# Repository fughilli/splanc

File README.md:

<p align="center">

</p>

**Map every LED in an addressable-LED installation in 3D — with just a phone —
then design light effects that flow across the real geometry and play them live
on the controller.**

Mount your LEDs however you like (a sculpture, a ceiling, a sign, a tree), walk
around the lit fixture with your phone, and splanc recovers the `(x, y, z)`
position of every LED. Then you author effects in a browser editor and stream
them to the device, where they run across the fixture's true 3D shape instead of
a guessed layout.

No ARCore, no LiDAR, no depth sensor — capture runs in any modern phone browser
(rear camera + motion sensors), and a visual-inertial solver estimates the
camera path and the LED positions together.

<p align="center">
  
  <br />
  <em>▶ Watch the intro video</em>
</p>

## Quickstart

**→ [The Splanc quickstart](./docs/quickstart.md)**: from a bare ESP32-C6
board to mapped, animated lights in a browser. The app is a PWA, nothing to
install: **<https://splanc.io/app>**.

1. **Wire it.** Any ESP32-C6 board (the C6 SuperMini is the reference), a
   WS2812/NeoPixel strip with its data on **GPIO20** (a second strip on
   GPIO14), and a 5 V supply for the strip with a common ground.
2. **Flash it.** Open the app in Chrome or Edge on a computer (or Chrome on
   Android; the iPhone app can't set up new hardware), tap **Flash new device
   (USB)**, then **Connect a board & flash**. No toolchain needed.
3. **Put it on Wi-Fi.** **Add device (Bluetooth)**: enter your Wi-Fi, pick the
   board, and accept its certificate once. From firmware 1.10.0 it remembers
   the network across reboots and updates.
4. **Map it.** **Maps ▸ + New**, then walk slowly around the lit fixture with
   your phone until the live preview converges. You get a 3D map of every LED.
5. **Play.** Pick or write an effect, perform in Show mode, bind MIDI knobs, or
   hand the lights to your AI agent (below).

## Ask an AI agent

Splanc players can also be driven by an AI agent. Tell an agent that has a shell
and Node.js 20 or later _"Use splanc.io to set the mood of the room"_. It reads
<https://splanc.io/AGENTS.md> and finds every Splanc fixture on your LAN. It
treats them as one room, with a shared room frame and clock, and can tweak the
running effect's knobs or write, preview and deploy a new effect.

To install it as an MCP server once:

```sh
claude mcp add splanc -- npx -y https://splanc.io/agent/splanc-agent.tgz
```

There is no LAN authentication, so anyone on your network can drive the lights.
See [`agent/README.md`](./agent/README.md).

## Hardware

- **Controller:** an **ESP32-C6** running the firmware in [`firmware/`](./firmware),
  or a **Raspberry Pi** (see [`pi/`](./pi)). The controller drives the LEDs, runs
  the effects VM, and serves the secure control channel.
- **LEDs:** addressable strips or pixels (SK9822 / APA102 / WS2812-family).
- **Capture device:** any phone with a rear camera and motion sensors
  (Android / Chrome is the primary target).

## How it works

1. **Blink code.** The controller drives the LEDs through a short, self-clocking
   color code that gives every LED a unique temporal signature.
2. **Capture.** You walk around the fixture with the phone. The camera decodes
   each LED's code frame-by-frame while the phone's motion sensors track its
   pose.
3. **Solve.** A visual-inertial bundle adjustment recovers each LED's 3D
   position (and the camera trajectory), metric-scaled and gravity-aligned.
4. **Topology.** The point cloud is turned into a skeleton — strands, segments,
   junctions and loops — so effects can address the fixture by its shape, not
   just its coordinates.
5. **Effects.** You write GLSL-ish shaders in the browser editor (per-LED
   position, segment, distance fields, textures), preview them live, and the
   compiler emits compact bytecode.
6. **Play.** The bytecode runs on the controller's effects VM, streamed over a
   secure WebSocket — so what you see in the editor is what lights up.

## Learn more

- **Quickstart:** [`docs/quickstart.md`](./docs/quickstart.md) — wiring,
  flashing, Wi-Fi, mapping, effects and agents, one short section each
- **Using the app:** [`docs/user-guide.md`](./docs/user-guide.md) — a walkthrough of
  every feature (also an interactive tutorial in the app, from Settings ▸ Help)
- **Why it's built this way:** [the Splanc manifesto](./docs/manifesto.md):
  a microcontroller instead of Art-Net boxes, our own wireless stack, no heap,
  and model checking for an LED controller.
- **What's new:** [`docs/whats-new.md`](./docs/whats-new.md)
- **Contributing & building from source:** [`DEVELOPERS.md`](./DEVELOPERS.md)
- **Design & architecture:** [`led-mapper-design.md`](./led-mapper-design.md) —
  the durable spec — plus [`docs/`](./docs)
- **Project history / build log:** [`WORKLOG.md`](./WORKLOG.md)

## License

Splanc is free and open-source software, licensed under the
**[GNU Affero General Public License v3.0](./LICENSE)** (AGPL-3.0). Two subtrees
are carved out under the permissive **MIT License** so anyone can build
compatible projects against the wire protocol:

- **`shared/protocol/`** — the LED Mapper wire protocol (schemas, `.proto`, and
  the generated TypeScript/Python/Rust bindings).
- **`tools/touchdesigner/`** — the TouchDesigner client binding.

See [`LICENSING.md`](./LICENSING.md) for the full map. Contributions are welcome
under a [Contributor License Agreement](./CLA.md); start with
[`CONTRIBUTING.md`](./CONTRIBUTING.md).

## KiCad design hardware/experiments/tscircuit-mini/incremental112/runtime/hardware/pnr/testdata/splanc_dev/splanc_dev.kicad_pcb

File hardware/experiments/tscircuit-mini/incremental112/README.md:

# Incremental placement candidate evaluation

Clones the incumbent routed PCB, not the original unrouted source. The requested
run is seeded from full109's completed round01 (85 native opens, zero violations;
153 subwidth tracks and one unqualified pair remain). No baseline reroute.

incremental_place.py peels copper leaves touching moved pads back to the first
shared junction/stationary pad, preserves shared trunks, then invalidates exact
layer-aware pad/drill clearance conflicts at the destination. It retains all
unaffected track/via UUIDs and normalized geometry, plane definitions, outline,
and native footprint/pad identities. Bodies do not blanket-delete inner copper.
Locked copper and source-sized power arrays fail closed. Affected pairs are
invalidated together and their stale reference witnesses removed. The prototype
rejects outline changes and source-array/keepout owner relocation.

Full electrical phases continue against retained copper. Existing arrays are
retained; planes refill. Staged signals use fixed copper. Final candidate guards
compare original pad connectivity and qualified entries with the repaired board;
open-count improvement cannot conceal loss of a previously connected group.
The winner becomes the routed seed for the next round only on acceptance.
Each phase is captured, including the routed seed and local invalidation with
removed UUID/reason metadata. Batch111 deferred native DRC validation is included.

Tests: three native geometry regressions (shared T trunk/layer separation,
destination conflict, no-op exact copper). Real first-round C1 translation keeps
2043/2048 copper items. Real no-op keeps all2048 and native85opens/0violations.
Controller preflight resumes round2 with one completed round. Full experimental
routing and final visual/electrical qualification remain in progress.

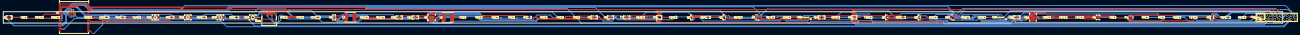
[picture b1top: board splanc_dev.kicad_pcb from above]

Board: 2 copper layers, 787.0 x 7.0 mm, 79 parts (0 on the bottom side), 54 nets.

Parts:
C1, C2, C3, C4, C8, C9, C12, C13, C14, C16, C17, C19, C20, C22, C23, C24, C25, C26: C0402
C5, C6, C7, C10, C11, C18, C21: C0805
C15, C27: C0603
CN1: CONN-TH_B2B-PH-K-S
CN2, CN3: CONN-TH_B3B-PH-K-S
H1: HDR-TH_20P-P2.54-V-M-R2-C10-S2.54
L1: L0805
L2, L3: IND-SMD_L6.0-W6.0_SWPA6045S
Q1, Q3: SOT-23-3_L2.9-W1.3-P1.90-LS2.4-BR
Q2, Q4: SOT-23_L2.9-W1.3-P1.90-LS2.4-BR
R1, R2, R3, R6, R7, R8, R9, R11, R12, R14, R16, R17, R18, R20, R21, R22, R23: R0402
R4, R5, R10, R13, R15, R19, R24, R25: R0603
SW1, SW2, SW3, SW4: SW-SMD_L3.9-W3.0-P4.45
U1: LGA-8_L2.5-W2.0-P0.65_AMP6127
U2: VQFN-20_L4.6-W3.6-P0.50-BL
U3: SOT-23-5_L3.0-W1.7-P0.95-LS2.8-BR
U4: SOT-23-5_L3.0-W1.7-P0.95-LS2.8-BL
U5: WIRELM-SMD_ESP32-C6-WROOM-1
U6: TDFN-8_L2.0-W2.0-P0.50-BL-EP1.2
U7, U9: MSOP-10_L3.0-W3.0-P0.50-LS5.0-BL
U8, U10: SOT-23-6_L2.9-W1.6-P0.95-LS2.8-BR
U11: QFN-24_L4.0-W4.0-P0.50-BL-EP2.7
USB1: USB-C-SMD_TYPE-C-16PIN-2MD-073

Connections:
1: H1.16, R5.2, SW1.1, U5.15
1-1: H1.17, R24.2, SW3.1, U5.20
1-2: H1.18, R25.2, SW4.1, U5.21
13: U5.13, USB1.A7, USB1.B7
14: U5.14, USB1.A6, USB1.B6
19: H1.19, U5.25
20: H1.20, U5.24
A5: R6.1, USB1.A5
B: Q1.1, R14.2
B5: R7.1, USB1.B5
BOOT: C3.2, U2.8
C: Q1.3, Q2.1, R15.2
COMP: C4.1, U2.18
CPOUT: C24.1, U11.20
EN: U2.2, U5.11
EN-1: C14.1, H1.15, R10.2, SW2.1, U5.3
FB: R1.1, R2.2, U2.17
FB-1: R11.1, R12.2, U3.5
FSW: R3.1, U2.3
ILIM: R4.1, U2.19
INT: U5.19, U11.12
PROG: R8.1, U4.5
REGOUT: C26.1, U11.10
RESV: U11.19, U11.21, U11.22
S: Q2.2, R15.1, R16.2, U7.8, U7.9
SCL: H1.14, R22.2, U1.4, U5.7, U6.7, U7.5, U9.5, U11.23
SDA: H1.13, R23.2, U1.3, U5.6, U6.8, U7.4, U9.4, U11.24
SS: C8.1, U2.10
STAT: R9.2, U4.1
SW: C3.1, L2.2, U2.4, U2.5, U2.6, U2.7
SW-1: L3.1, U3.3
chan_out: CN3.1, H1.10, Q4.3
chan_out-1: CN2.1, H1.9, Q2.3
data_in: H1.11, U5.8, U8.3
data_in-1: H1.12, U5.9, U10.3
data_out: CN2.2, R17.2
en: R14.1, U5.27
en-1: R18.1, U5.4
fault: H1.7, U5.26, U7.3
fault-1: H1.8, U5.5, U9.3
hv: C1.1, C2.1, C25.1, L1.2, R22.1, R23.1, U1.2, U1.6, U1.8, U9.2, U11.8, U11.13
led0-B: R17.1, U8.4
led1-B: Q3.1, R18.2
led1-B-1: R21.1, U10.4
led1-C: Q3.3, Q4.1, R19.2
led1-S: Q4.2, R19.1, R20.2, U9.8, U9.9
led1-data_out: CN3.2, R21.2
lv: C1.2, C2.2, C4.2, C5.2, C6.2, C7.2, C8.2, C9.2, C10.2, C11.2, C12.2, C13.2, C14.2, C15.2, C16.2, C17.2, C18.2, C19.2, C20.2, C21.2, C22.2, C23.2, C24.2, C25.2, C26.2, C27.2, CN1.2, CN2.3, CN3.3, H1.2, Q1.2, Q3.2, R1.2, R3.2, R4.2, R6.2, R7.2, R8.2, R11.2, SW1.2, SW2.2, SW3.2, SW4.2, U1.1, U1.5, U1.7, U2.13, U2.20, U2.21, U4.2, U5.1, U5.28, U5.29, U5.30, U5.31, U5.32, U5.33, U5.34, U5.35, U5.36, U5.37, U6.9, U7.1, U7.2, U7.7, U8.2, U9.1, U9.7, U10.2, U11.9, U11.18, USB1.13, USB1.14
nALRT: R13.2, U6.5
p3v3-hv: C11.1, C15.1, C16.1, C19.1, C22.1, H1.6, L1.1, L3.2, R5.1, R9.1, R10.1, R12.1, R13.1, R24.1, R25.1, U5.2, U7.6, U8.1, U9.6, U10.1
p5v-hv: C6.1, C7.1, C18.1, C20.1, C21.1, C23.1, H1.5, R2.1, R16.1, R20.1, U2.14, U2.15, U2.16, U7.10, U8.5, U8.6, U9.10, U10.5, U10.6
usbc-GND: USB1.A1B12, USB1.B1A12
vbat-hv: C13.1, C17.1, CN1.1, H1.4, U4.3, U6.2, U6.3
vsys-hv: C5.1, C9.1, C10.1, C12.1, C27.1, H1.1, H1.3, L2.1, U2.1, U2.9, U3.1, U3.4, U4.4, USB1.A4B9, USB1.B4A9
